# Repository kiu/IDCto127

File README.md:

# IDCto127
SMD IDC 2.54mm to 1.27mm adapter

# License
This project is licensed under the Creative Commons Attribution-NonCommercial 3.0 Unported (CC BY-NC 3.0) license.

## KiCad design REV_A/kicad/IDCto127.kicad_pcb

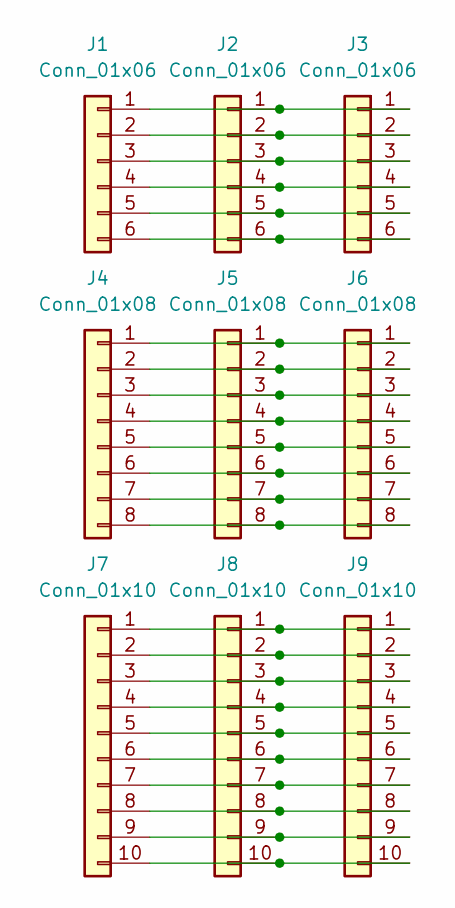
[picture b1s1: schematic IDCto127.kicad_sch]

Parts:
J1: Conn_01x06; IDC-Header_2x03_P2.54mm_Vertical_SMD; LCSC C42372545
J2: Conn_01x06; PinHeader_1x06_P2.54mm_Vertical_SMD_Pin1Left; LCSC C5160789
J3: Conn_01x06; IDC-Header_2x03_P1.27mm_Vertical_SMD; LCSC C42372553
J4: Conn_01x08; IDC-Header_2x04_P2.54mm_Vertical_SMD; LCSC C42372546
J5: Conn_01x08; PinHeader_1x08_P2.54mm_Vertical_SMD_Pin1Left; LCSC C5160791
J6: Conn_01x08; IDC-Header_2x04_P1.27mm_Vertical_SMD; LCSC C42372554
J7: Conn_01x10; IDC-Header_2x05_P2.54mm_Vertical_SMD; LCSC C5665
J8: Conn_01x10; PinHeader_1x10_P2.54mm_Vertical_SMD_Pin1Left; LCSC C42453977
J9: Conn_01x10; IDC-Header_2x05_P1.27mm_Vertical_SMD; LCSC C42372555

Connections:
unnamed: J1.1, J2.1, J3.1
unnamed: J1.2, J2.2, J3.2
unnamed: J1.3, J2.3, J3.3
unnamed: J1.4, J2.4, J3.4
unnamed: J1.5, J2.5, J3.5
unnamed: J1.6, J2.6, J3.6
unnamed: J4.1, J5.1, J6.1
unnamed: J4.2, J5.2, J6.2
unnamed: J4.3, J5.3, J6.3
unnamed: J4.4, J5.4, J6.4
unnamed: J4.5, J5.5, J6.5
unnamed: J4.6, J5.6, J6.6
unnamed: J4.7, J5.7, J6.7
unnamed: J4.8, J5.8, J6.8
unnamed: J7.1, J8.1, J9.1
unnamed: J7.2, J8.2, J9.2
unnamed: J7.3, J8.3, J9.3
unnamed: J7.4, J8.4, J9.4
unnamed: J7.5, J8.5, J9.5
unnamed: J7.6, J8.6, J9.6
unnamed: J7.7, J8.7, J9.7
unnamed: J7.8, J8.8, J9.8
unnamed: J7.9, J8.9, J9.9
unnamed: J7.10, J8.10, J9.10

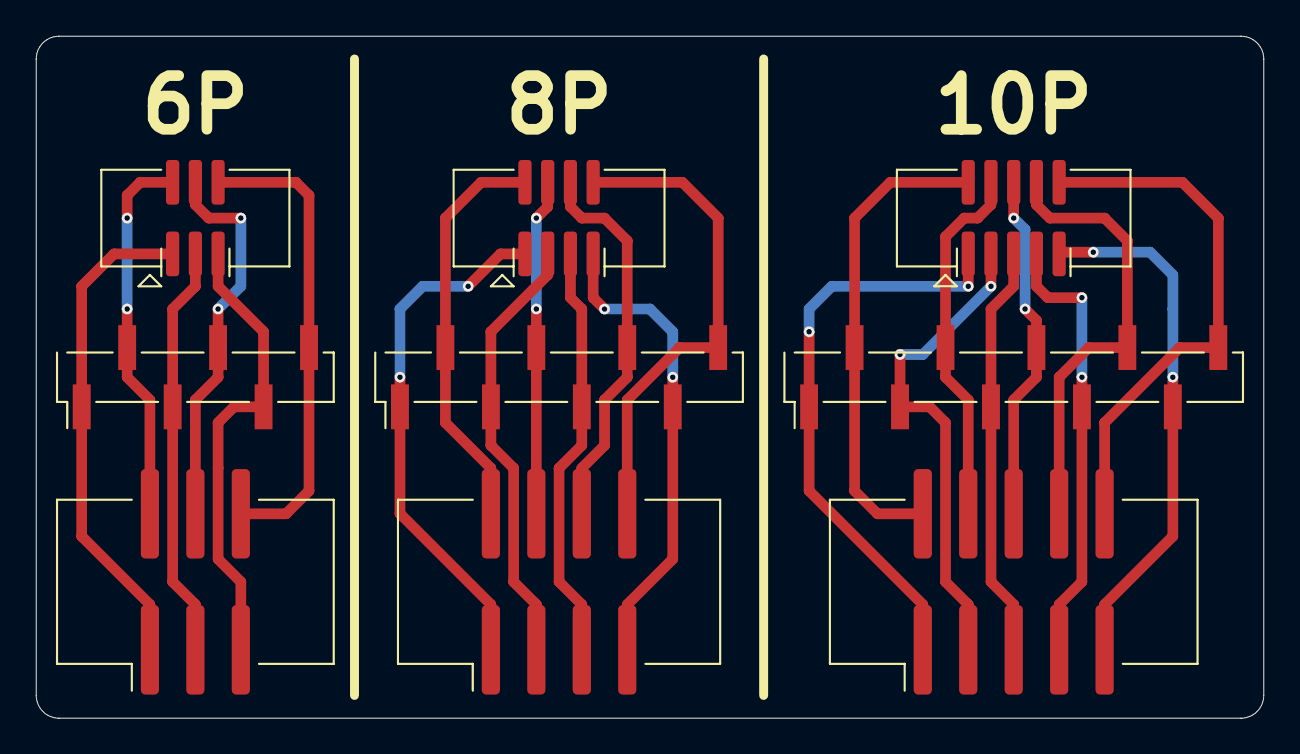
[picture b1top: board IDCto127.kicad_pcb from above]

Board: 2 copper layers, 68.6 x 38.1 mm, 9 parts (0 on the bottom side), 24 nets.

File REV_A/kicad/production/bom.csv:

Designator,Footprint,Quantity,Value,LCSC Part #
J1,IDC-Header_2x03_P2.54mm_Vertical_SMD,1,Conn_01x06,C42372545
J2,PinHeader_1x06_P2.54mm_Vertical_SMD_Pin1Left,1,Conn_01x06,C5160789
J3,IDC-Header_2x03_P1.27mm_Vertical_SMD,1,Conn_01x06,C42372553
J4,IDC-Header_2x04_P2.54mm_Vertical_SMD,1,Conn_01x08,C42372546
J5,PinHeader_1x08_P2.54mm_Vertical_SMD_Pin1Left,1,Conn_01x08,C5160791
J6,IDC-Header_2x04_P1.27mm_Vertical_SMD,1,Conn_01x08,C42372554
J7,IDC-Header_2x05_P2.54mm_Vertical_SMD,1,Conn_01x10,C5665
J8,PinHeader_1x10_P2.54mm_Vertical_SMD_Pin1Left,1,Conn_01x10,C42453977
J9,IDC-Header_2x05_P1.27mm_Vertical_SMD,1,Conn_01x10,C42372555

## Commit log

2026-03-03 Updated broken IDC127 footprint (missing paste layer)
